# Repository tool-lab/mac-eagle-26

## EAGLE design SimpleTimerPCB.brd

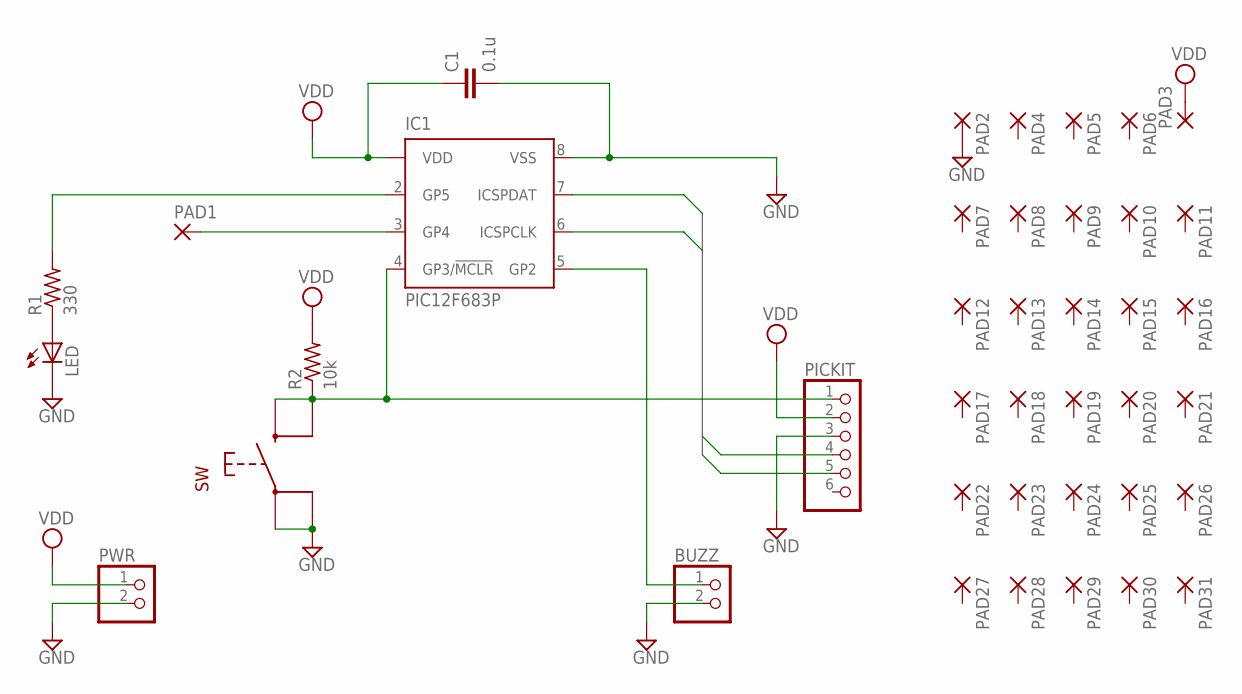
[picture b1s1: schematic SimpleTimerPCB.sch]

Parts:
BUZZ: PINHD-1X2; 1X02
C1: 0.1u; C050-024X044
IC1: PIC12F683P; DIL8
LED: LED3MM
PAD1, PAD2, PAD3, PAD4, PAD5, PAD6, PAD7, PAD8, PAD9, PAD10, PAD11, PAD12, PAD13, PAD14, PAD15, PAD16, PAD17, PAD18, PAD19, PAD20, PAD21, PAD22, PAD23, PAD24, PAD25, PAD26, PAD27, PAD28, PAD29, PAD30, PAD31: 1,6/0,9
PICKIT: PINHD-1X6; 1X06
PWR: PINHD-1X2; 1X02
R1: 330; 0204/7
R2: 10k; 0204/7
SW: TACT-SWITCH; TACTSW-25X20

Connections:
GND: BUZZ.2, C1.2, IC1.8 (VSS), LED.K (C), PAD2.1, PICKIT.3, PWR.2, SW.3 (P1), SW.4 (P2)
unnamed: LED.A, R1.1
unnamed: IC1.4 (GP3/!MCLR!), PICKIT.1, R2.1, SW.1 (S1), SW.2 (S2)
unnamed: IC1.3 (GP4), PAD1.1
unnamed: IC1.2 (GP5), R1.2
unnamed: BUZZ.1, IC1.5 (GP2)
PIN4: IC1.7 (ICSPDAT), PICKIT.4
PIN5: IC1.6 (ICSPCLK), PICKIT.5
VDD: C1.1, IC1.1 (VDD), PAD3.1, PICKIT.2, PWR.1, R2.2

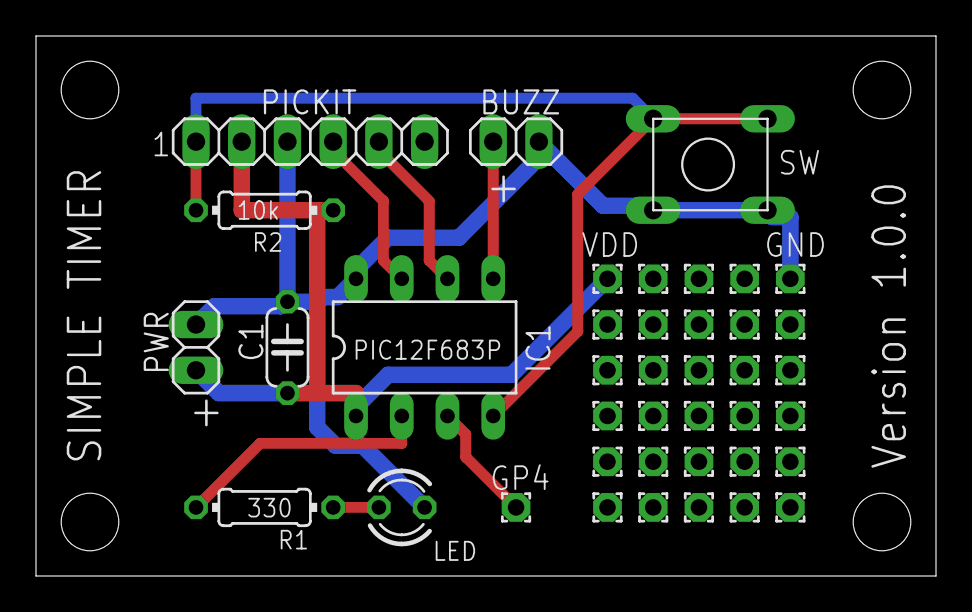
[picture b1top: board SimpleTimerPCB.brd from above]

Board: 2 copper layers, 50.0 x 30.0 mm, 40 parts (0 on the bottom side), 9 nets.
